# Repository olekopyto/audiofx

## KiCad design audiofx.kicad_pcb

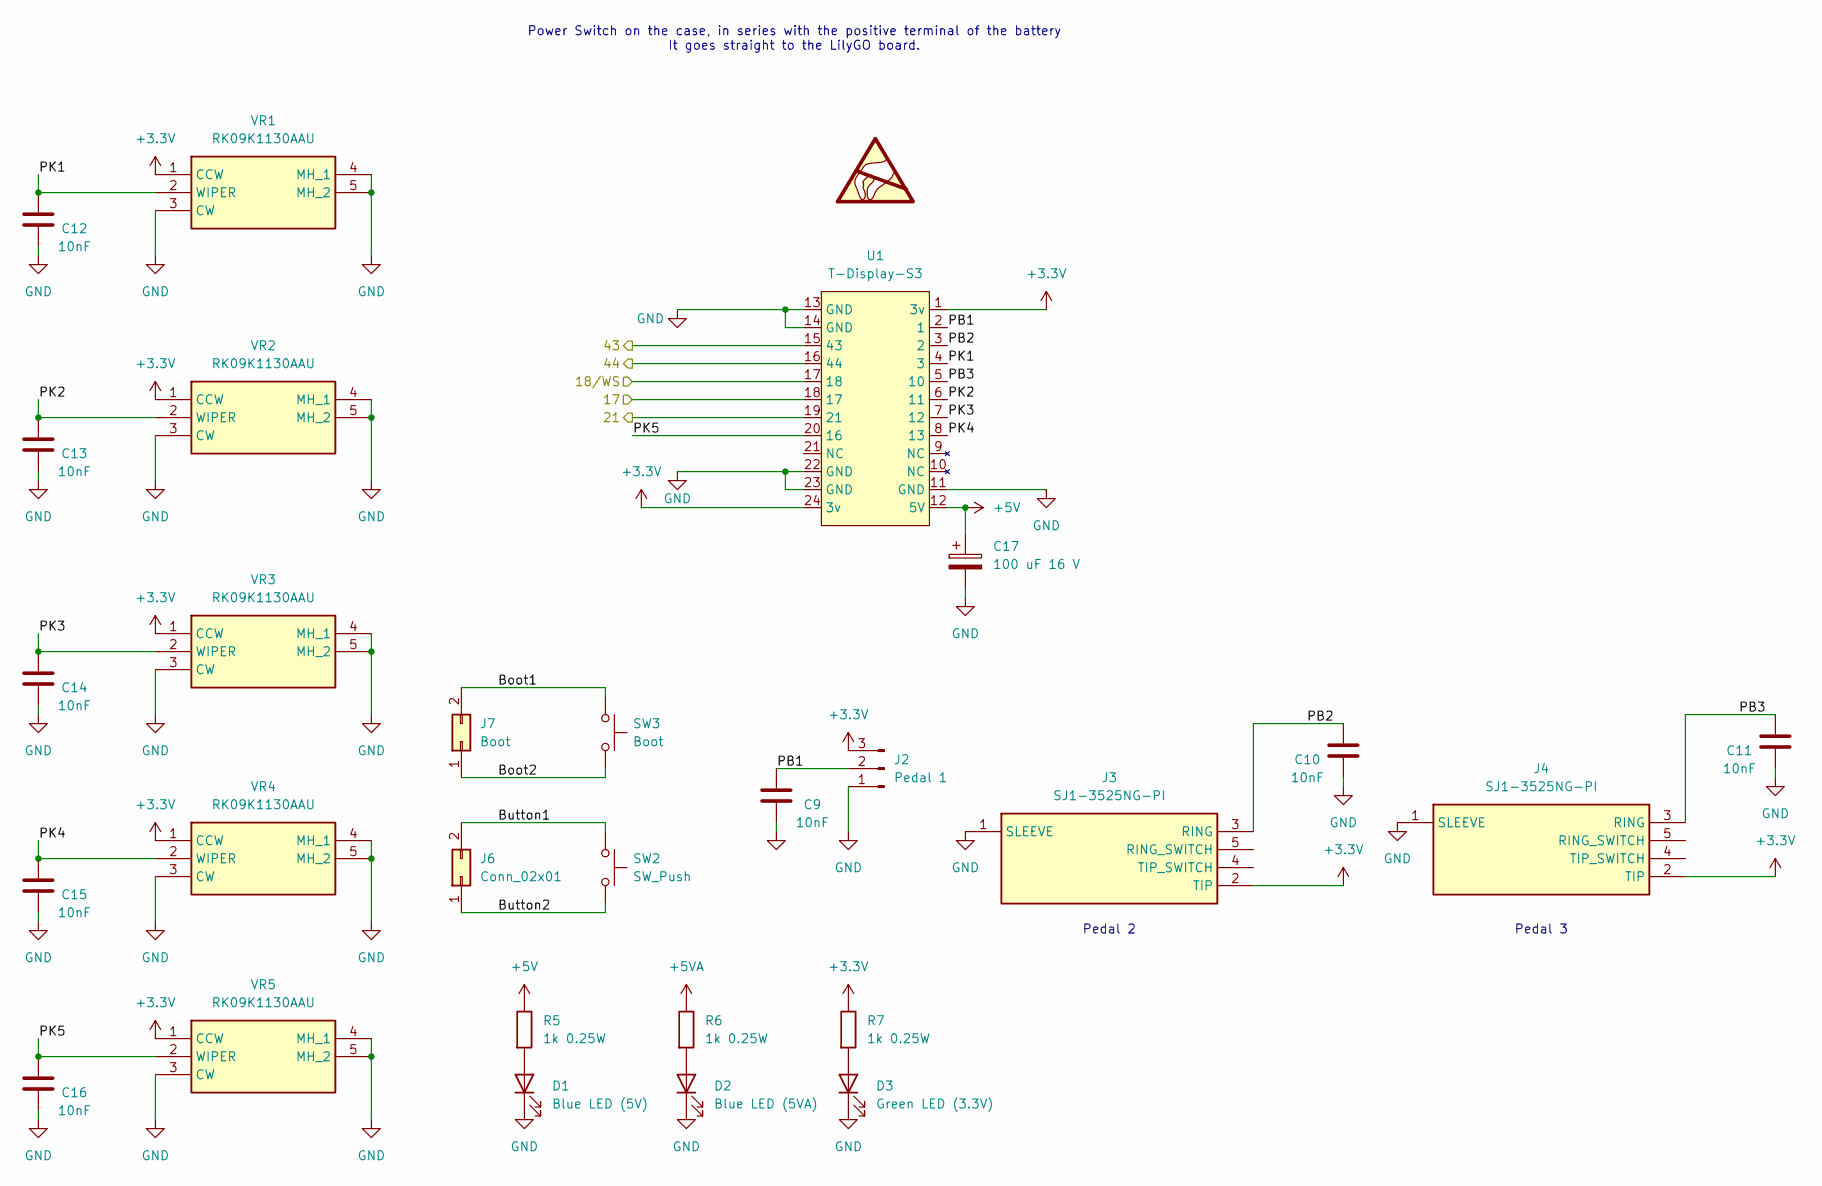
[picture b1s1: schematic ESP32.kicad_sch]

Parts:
C9, C10, C11, C12, C13, C14, C15, C16: 10nF; C_0805_2012Metric_Pad1.18x1.45mm_HandSolder
C17: 100 uF 16 V; CP_Radial_D10.0mm_P5.00mm
D1: Blue LED (5V); LED_D5.0mm
D2: Blue LED (5VA); LED_D5.0mm
D3: Green LED (3.3V); LED_D5.0mm
J2: Pedal 1; PinSocket_1x03_P2.54mm_Vertical
J3, J4: SJ1-3525NG-PI; SJ13525NGPI; Mouser Part Number 490-SJ1-3525NG-PI
J6: Conn_02x01; PinHeader_2x01_P2.54mm_Vertical
J7: Boot; PinHeader_2x01_P2.54mm_Vertical
R5, R6, R7: 1k 0.25W; R_Axial_DIN0204_L3.6mm_D1.6mm_P5.08mm_Horizontal
SW2: SW_Push; SW_PUSH_6mm_H13mm
SW3: Boot; SW_PUSH_6mm_H13mm
U1: T-Display-S3
VR1, VR2, VR3, VR4, VR5: RK09K1130AAU; Mouser Part Number 688-RK09K1130AAU

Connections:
+3.3V: J2.3, J3.2 (TIP), J4.2 (TIP), R7.1, U1.1 (3v), U1.24 (3v), VR1.1 (CCW), VR2.1 (CCW), VR3.1 (CCW), VR4.1 (CCW), VR5.1 (CCW); also elsewhere on the board
+5V: C17.1, R5.1, U1.12 (5V)
+5VA: R6.1; also elsewhere on the board
/ESP32/17: U1.18 (17); also elsewhere on the board
/ESP32/18/WS: U1.17 (18); also elsewhere on the board
/ESP32/21: U1.19 (21); also elsewhere on the board
/ESP32/43: U1.15 (43); also elsewhere on the board
/ESP32/44: U1.16 (44); also elsewhere on the board
/ESP32/Boot1: J7.2, SW3.1
/ESP32/Boot2: J7.1, SW3.2
/ESP32/Button1: J6.2, SW2.1
/ESP32/Button2: J6.1, SW2.2
/ESP32/PB1: C9.1, J2.2, U1.2 (1)
/ESP32/PB2: C10.1, J3.3 (RING), U1.3 (2)
/ESP32/PB3: C11.1, J4.3 (RING), U1.5 (10)
/ESP32/PK1: C12.1, U1.4 (3), VR1.2 (WIPER)
/ESP32/PK2: C13.1, U1.6 (11), VR2.2 (WIPER)
/ESP32/PK3: C14.1, U1.7 (12), VR3.2 (WIPER)
/ESP32/PK4: C15.1, U1.8 (13), VR4.2 (WIPER)
/ESP32/PK5: C16.1, U1.20 (16), VR5.2 (WIPER)
GND: C9.2, C10.2, C11.2, C12.2, C13.2, C14.2, C15.2, C16.2, C17.2, D1.1 (K), D2.1 (K), D3.1 (K), J2.1, J3.1 (SLEEVE), J4.1 (SLEEVE), U1.11 (GND), U1.13 (GND), U1.14 (GND), U1.22 (GND), U1.23 (GND), VR1.3 (CW), VR1.4 (MH_1), VR1.5 (MH_2), VR2.3 (CW), VR2.4 (MH_1), VR2.5 (MH_2), VR3.3 (CW), VR3.4 (MH_1), VR3.5 (MH_2), VR4.3 (CW), VR4.4 (MH_1), VR4.5 (MH_2), VR5.3 (CW), VR5.4 (MH_1), VR5.5 (MH_2); also elsewhere on the board
unnamed: D1.2 (A), R5.2
unnamed: D2.2 (A), R6.2
unnamed: D3.2 (A), R7.2

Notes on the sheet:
Pedal 3
Power Switch on the case, in series with the positive terminal of the battery It goes straight to the LilyGO board.
Pedal 2

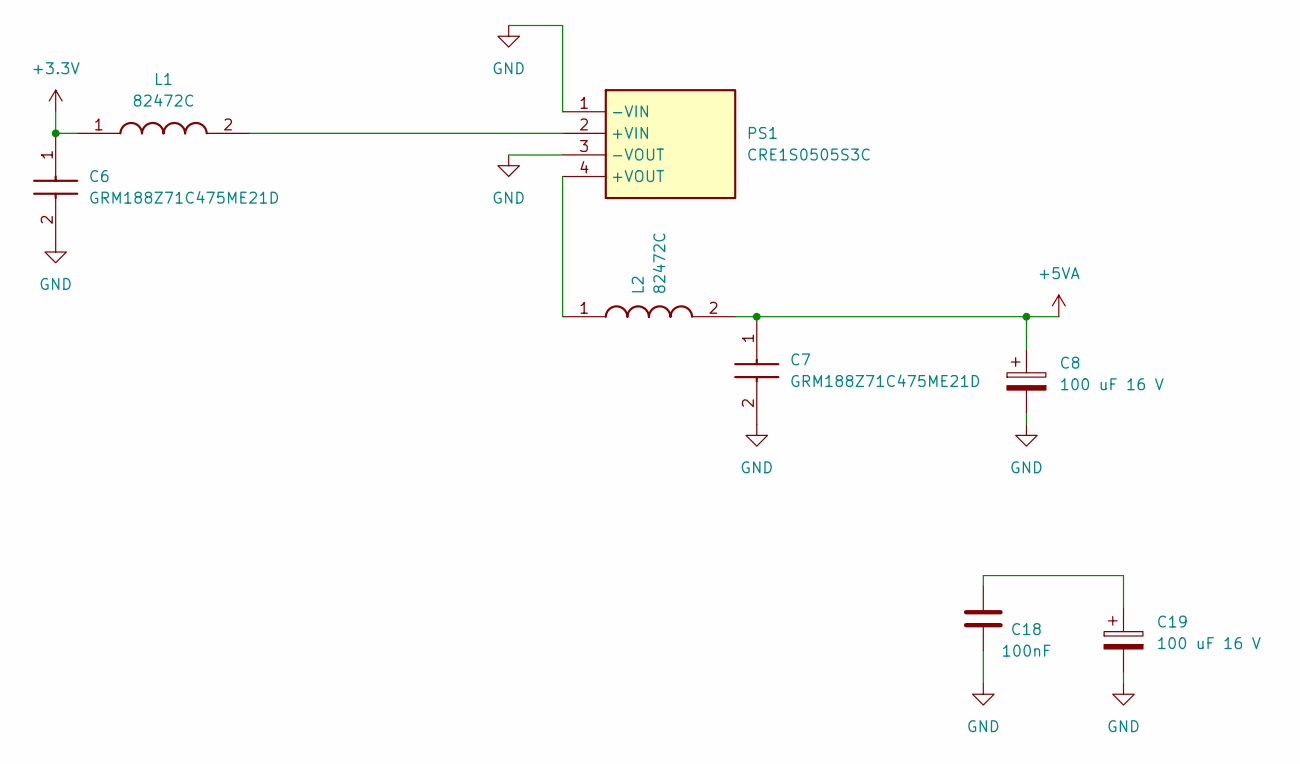
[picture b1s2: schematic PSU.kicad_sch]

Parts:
C6, C7: GRM188Z71C475ME21D; C_0603_1608Metric_Pad1.08x0.95mm_HandSolder; Mouser Part Number 81-GRM188Z71C475ME1D
C8, C19: 100 uF 16 V; CP_Radial_D10.0mm_P5.00mm
C18: 100nF; C_Disc_D3.0mm_W1.6mm_P2.50mm
L1, L2: 82472C; L_1210_3225Metric_Pad1.42x2.65mm_HandSolder; Mouser Part Number 580-82472C
PS1: CRE1S0505S3C; FanPinHeader_1x04_P2.54mm_Vertical; Mouser Part Number 580-CRE1S0505S3C

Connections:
+3.3V: C6.1, L1.1; also elsewhere on the board
+5VA: C7.1, C8.1, L2.2; also elsewhere on the board
GND: C6.2, C7.2, C8.2, C18.2, C19.2, PS1.1 (-VIN), PS1.3 (-VOUT); also elsewhere on the board
unnamed: C18.1, C19.1
unnamed: L1.2, PS1.2 (+VIN)
unnamed: L2.1, PS1.4 (+VOUT)

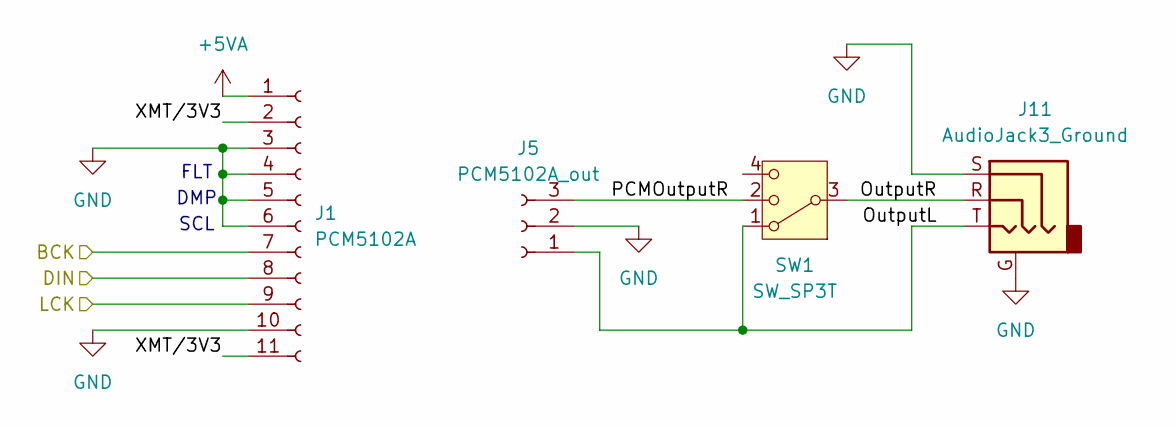
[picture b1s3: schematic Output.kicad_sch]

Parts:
J1: PCM5102A; PinSocket_1x11_P2.54mm_Vertical
J5: PCM5102A_out; PinSocket_1x03_P2.54mm_Vertical
J11: AudioJack3_Ground; Jack_6.35mm_Neutrik_NRJ3HF-1_Horizontal
SW1: SW_SP3T; SW_SP3T_PCM13

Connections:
+5VA: J1.1; also elsewhere on the board
/ESP32/17: J1.7; also elsewhere on the board
/ESP32/18/WS: J1.9; also elsewhere on the board
/ESP32/21: J1.8; also elsewhere on the board
/Output/OutputL: J5.1, J11.T, SW1.1
/Output/OutputR: J11.R, SW1.3
/Output/PCMOutputR: J5.3, SW1.2
/Output/XMT/3V3: J1.2, J1.11
GND: J1.3, J1.4, J1.5, J1.6, J1.10, J5.2, J11.G, J11.S; also elsewhere on the board

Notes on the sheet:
DMP
SCL
FLT

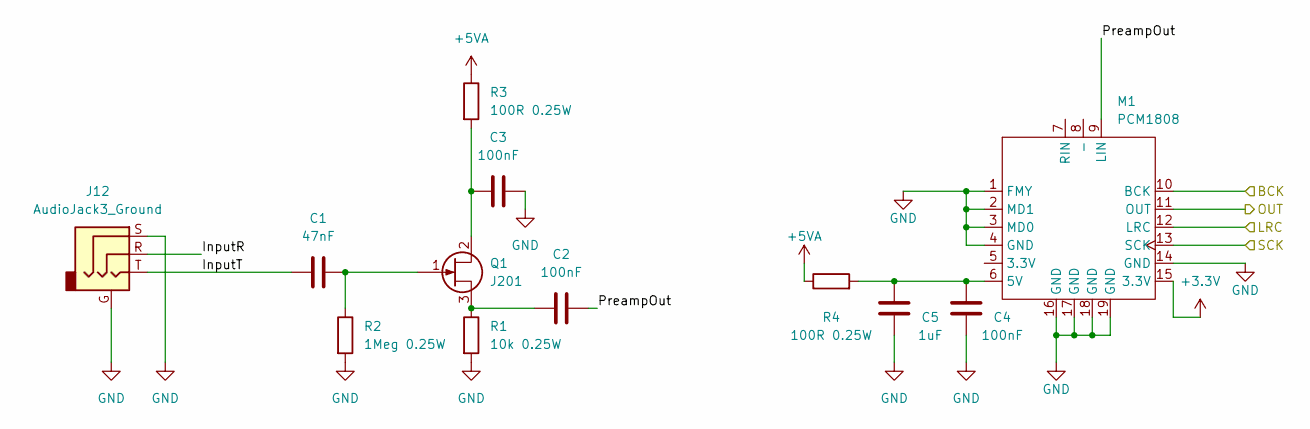
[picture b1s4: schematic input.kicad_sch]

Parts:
C1: 47nF; C_Disc_D3.0mm_W1.6mm_P2.50mm
C2, C3, C4: 100nF; C_Disc_D3.0mm_W1.6mm_P2.50mm
C5: 1uF; C_0805_2012Metric_Pad1.18x1.45mm_HandSolder
J12: AudioJack3_Ground; Jack_6.35mm_Neutrik_NRJ3HF-1_Horizontal
M1: PCM1808
Q1: J201; TO-92_HandSolder
R1: 10k 0.25W; R_Axial_DIN0204_L3.6mm_D1.6mm_P5.08mm_Horizontal
R2: 1Meg 0.25W; R_Axial_DIN0204_L3.6mm_D1.6mm_P5.08mm_Horizontal
R3, R4: 100R 0.25W; R_Axial_DIN0204_L3.6mm_D1.6mm_P5.08mm_Horizontal

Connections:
+3.3V: M1.15 (3.3V); also elsewhere on the board
+5VA: R3.1, R4.1; also elsewhere on the board
/ESP32/17: M1.11 (OUT); also elsewhere on the board
/ESP32/18/WS: M1.12 (LRC); also elsewhere on the board
/ESP32/43: M1.13 (SCK); also elsewhere on the board
/ESP32/44: M1.10 (BCK); also elsewhere on the board
/Input/InputR: J12.R
/Input/InputT: C1.1, J12.T
/Input/PreampOut: C2.2, M1.9 (LIN)
GND: C3.2, C4.2, C5.2, J12.G, J12.S, M1.1 (FMY), M1.2 (MD1), M1.3 (MD0), M1.4 (GND), M1.14 (GND), M1.16 (GND), M1.17 (GND), M1.18 (GND), M1.19 (GND), R1.2, R2.2; also elsewhere on the board
unnamed: C4.1, C5.1, M1.6 (5V), R4.2
unnamed: C3.1, Q1.2 (D), R3.2
unnamed: C1.2, Q1.1 (G), R2.1
unnamed: C2.1, Q1.3 (S), R1.1

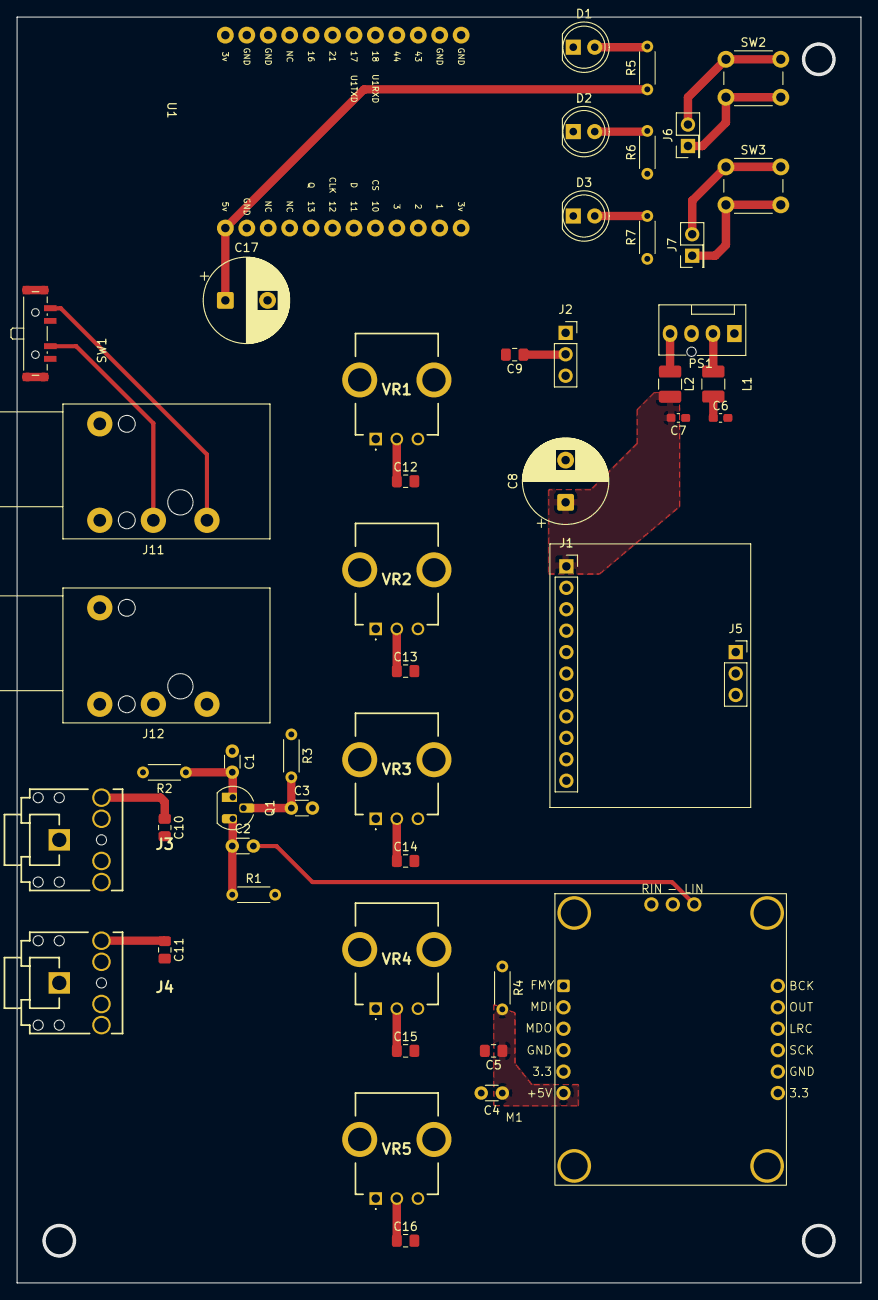
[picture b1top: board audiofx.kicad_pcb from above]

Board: 2 copper layers, 100.0 x 150.0 mm, 50 parts (0 on the bottom side), 36 nets.
